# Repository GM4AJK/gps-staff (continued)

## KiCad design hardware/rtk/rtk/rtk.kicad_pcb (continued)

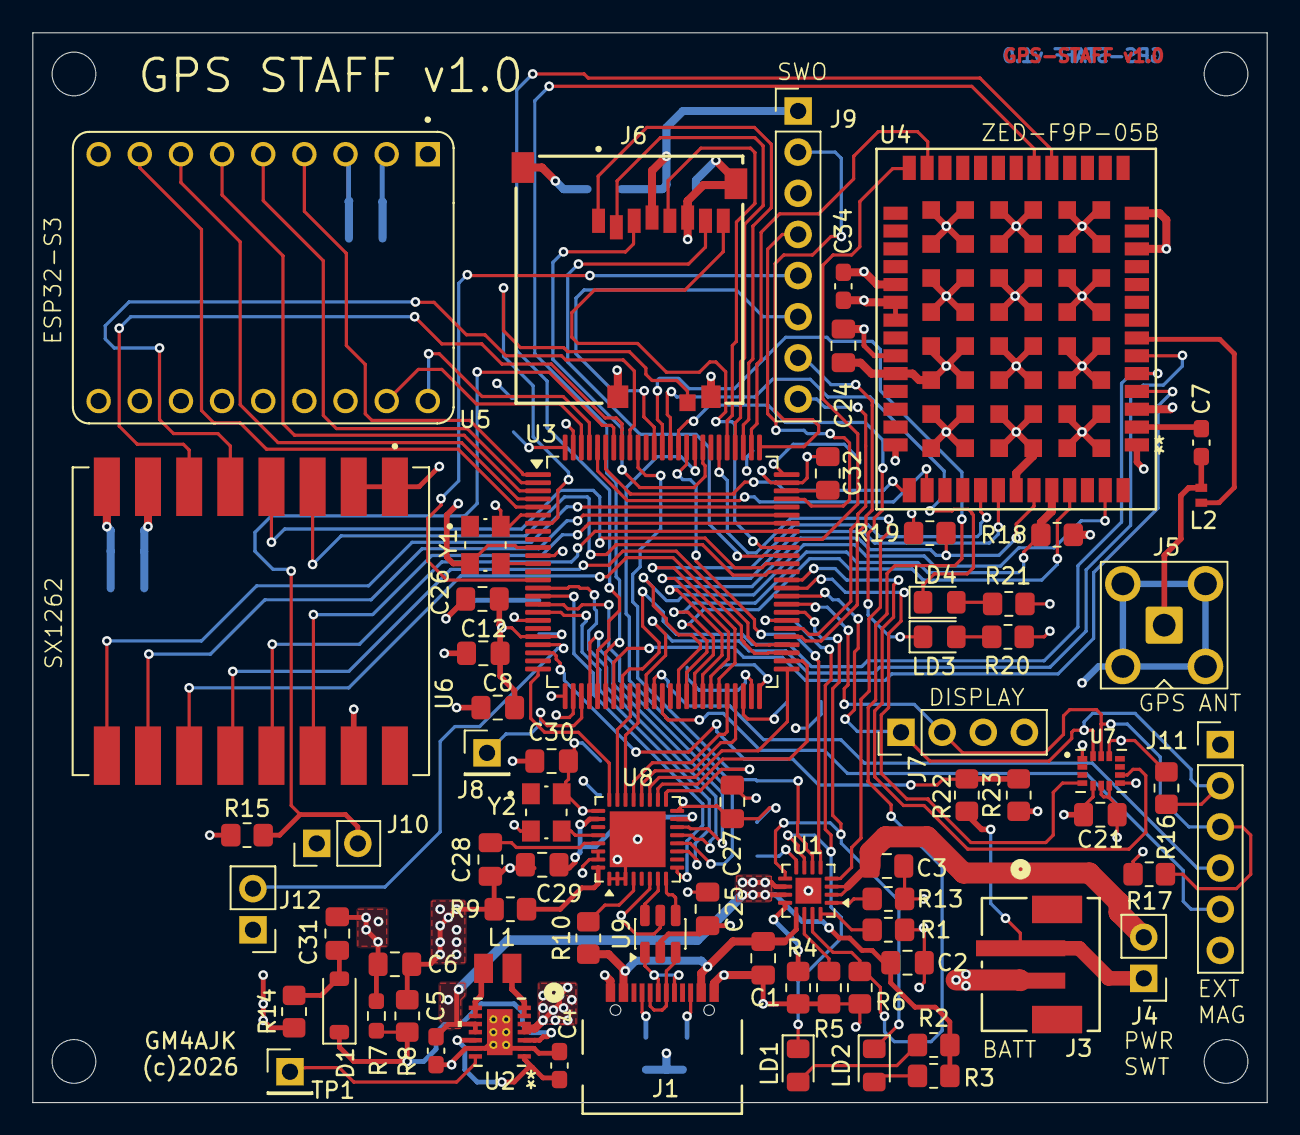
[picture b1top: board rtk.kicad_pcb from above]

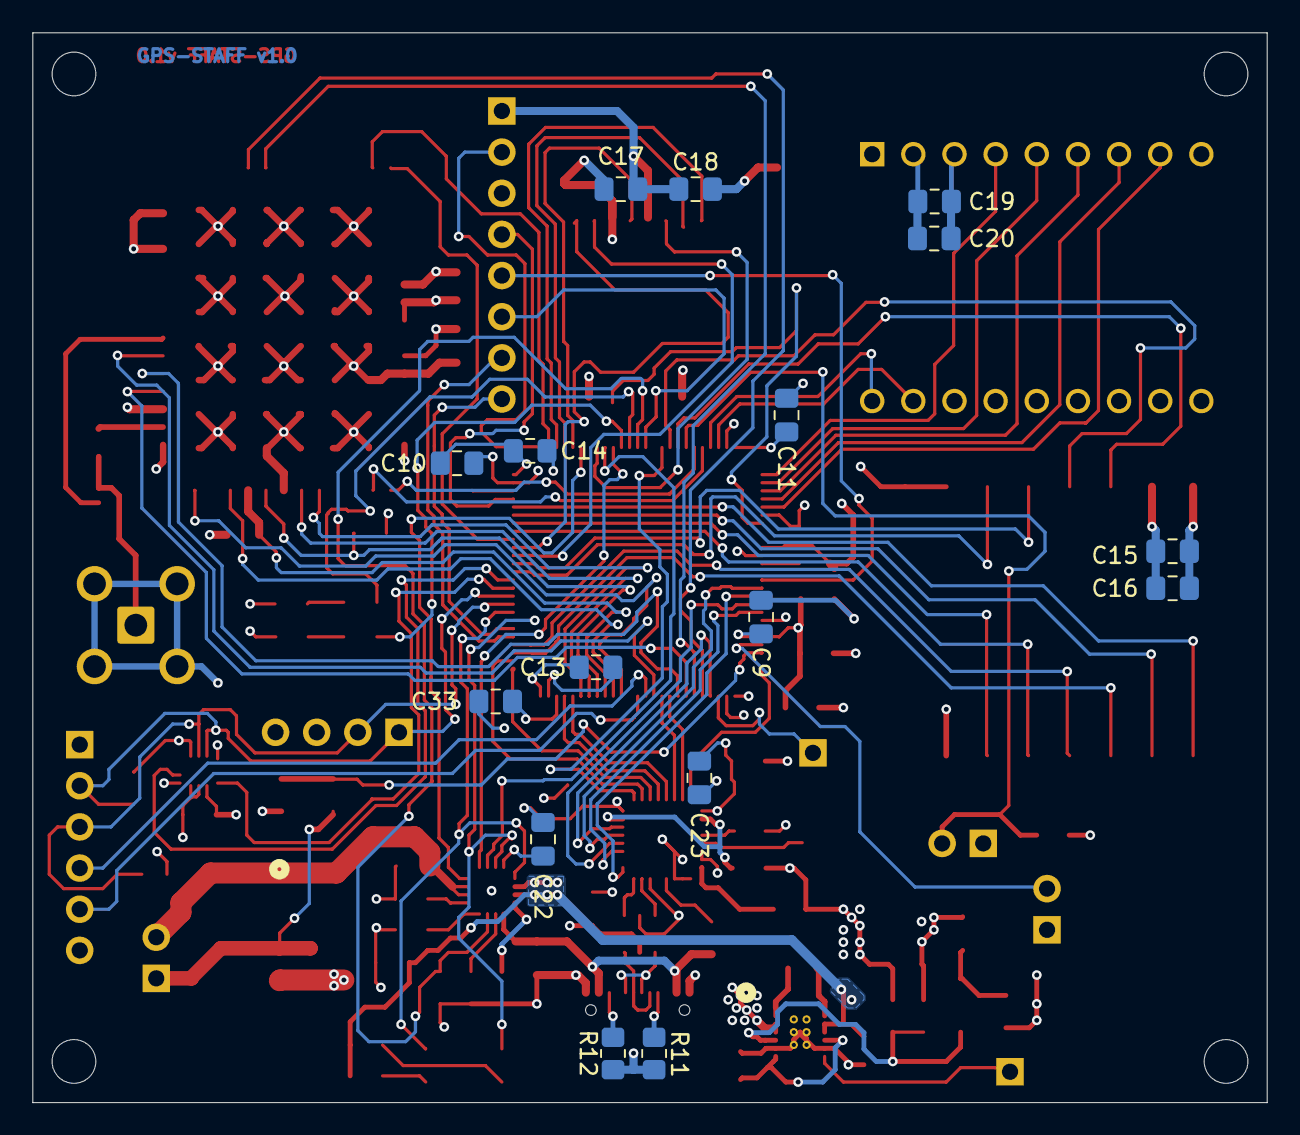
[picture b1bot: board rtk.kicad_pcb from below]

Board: 4 copper layers, 76.2 x 66.0 mm, 91 parts (16 on the bottom side), 113 nets.

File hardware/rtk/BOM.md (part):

# Schematic BOM — rtk PCB

Generated from KiCad schematics. One row per reference designator.
**Purpose:** footprint audit before PCB layout — verify every footprint against the actual part's datasheet land pattern.

Key:
- **Footprint** — KiCad library:footprint as currently assigned in the schematic
- **⚠** — suspected issue, needs checking before layout

---

## Capacitors

| Ref | Value | Footprint | Sheet | Notes |
|-----|-------|-----------|-------|-------|
| C1 | 1u | `C_0805_2012Metric_Pad1.18x1.45mm_HandSolder` | power | Tantallum (TAJR105M016RNJ) — verify 0805 land pattern matches AVX/Kyocera footprint |
| C2 | 4u7 | `C_0805_2012Metric_Pad1.18x1.45mm_HandSolder` | power | Tantalum (TAJP475K016RNJ) — same as C1 |
| C3 | 4u7 | `C_0805_2012Metric_Pad1.18x1.45mm_HandSolder` | power | Tantalum (TAJP475K016RNJ) — same as C1 |
| C4 | 100n | `C_0603_1608Metric_Pad1.08x0.95mm_HandSolder` | power | TPS63020 CvinA decoupling |
| C5 | 22u | `C_0603_1608Metric_Pad1.08x0.95mm_HandSolder` | power | TPS63020 Cin — part is C1608X5R1A226M080AC (0603/1608 metric) ✓ |
| C6 | 47u | `C_0805_2012Metric_Pad1.18x1.45mm_HandSolder` | power | TPS63020 Cout — part is MSASJ21GBB5476MTNA01 (0805/2012 metric) ✓ |
| C7 | 10n | `C_0603_1608Metric_Pad1.08x0.95mm_HandSolder` | zed-f9p-05b | VCC_RF decoupling |
| C8 | 100n | `C_0805_2012Metric_Pad1.18x1.45mm_HandSolder` | stm32f765vit | VDD decoupling |
| C9 | 100n | `C_0805_2012Metric_Pad1.18x1.45mm_HandSolder` | stm32f765vit | VDD decoupling |
| C10 | 100n | `C_0805_2012Metric_Pad1.18x1.45mm_HandSolder` | stm32f765vit | VDD decoupling |
| C11 | 100n | `C_0805_2012Metric_Pad1.18x1.45mm_HandSolder` | stm32f765vit | VDD decoupling |
| C12 | 100n | `C_0805_2012Metric_Pad1.18x1.45mm_HandSolder` | stm32f765vit | VDD decoupling |
| C13 | 100n | `C_0805_2012Metric_Pad1.18x1.45mm_HandSolder` | stm32f765vit | VDD decoupling |
| C14 | 100n | `C_0805_2012Metric_Pad1.18x1.45mm_HandSolder` | stm32f765vit | VDD decoupling |
| C15 | 100n | `C_0805_2012Metric_Pad1.18x1.45mm_HandSolder` | stm32f765vit | VDD decoupling |
| C16 | 10u | `C_0805_2012Metric_Pad1.18x1.45mm_HandSolder` | stm32f765vit | **T529P106M010AAE200** — Kemet KO-CAP polymer tant, 10µF 10V 0805, 200mΩ. Polarised symbol (C_Polarized_Small). ✓ |
| C17 | 100n | `C_0805_2012Metric_Pad1.18x1.45mm_HandSolder` | stm32f765vit | VDD decoupling |
| C18 | 10u | `C_0805_2012Metric_Pad1.18x1.45mm_HandSolder` | stm32f765vit | **T529P106M010AAE200** — same as C16 ✓ |
| C19 | 100n | `C_0805_2012Metric_Pad1.18x1.45mm_HandSolder` | stm32f765vit | VDD decoupling |
| C20 | 10u | `C_0805_2012Metric_Pad1.18x1.45mm_HandSolder` | stm32f765vit | **T529P106M010AAE200** — same as C16 ✓ |
| C21 | 100n | `C_0805_2012Metric_Pad1.18x1.45mm_HandSolder` | stm32f765vit | VDD decoupling |
| C22 | 100n | `C_0805_2012Metric_Pad1.18x1.45mm_HandSolder` | usb2hs | USB3300 decoupling |
| C23 | 100n | `C_0805_2012Metric_Pad1.18x1.45mm_HandSolder` | usb2hs | USB3300 decoupling |
| C24 | 100n | `C_0805_2012Metric_Pad1.18x1.45mm_HandSolder` | usb2hs | USB3300 decoupling |
| C25 | 100n | `C_0805_2012Metric_Pad1.18x1.45mm_HandSolder` | usb2hs | USB3300 decoupling |
| C26 | 100n | `C_0805_2012Metric_Pad1.18x1.45mm_HandSolder` | stm32f765vit | Decoupling |
| C27 | 100n | `C_0805_2012Metric_Pad1.18x1.45mm_HandSolder` | usb2hs | USB3300 decoupling |
| C28 | 470n | `C_0805_2012Metric_Pad1.18x1.45mm_HandSolder` | usb2hs | USB3300 VDD1.8 bulk |
| C29 | 470n | `C_0805_2012Metric_Pad1.18x1.45mm_HandSolder` | usb2hs | USB3300 VDD1.8 bulk |
| C30 | 100n | `C_0805_2012Metric_Pad1.18x1.45mm_HandSolder` | usb2hs | USB3300 decoupling |
| C31 | 10n | `C_0805_2012Metric_Pad1.18x1.45mm_HandSolder` | power | TPS63020 soft-start / inrush (C_SS) |
| C32 | 1u | `C_0805_2012Metric_Pad1.18x1.45mm_HandSolder` | stm32f765vit | STM32 VCAP_1 (internal LDO) |
| C33 | 1u | `C_0805_2012Metric_Pad1.18x1.45mm_HandSolder` | stm32f765vit | STM32 VCAP_2 (internal LDO) |
| C34 | 100n | `C_0603_1608Metric_Pad1.08x0.95mm_HandSolder` | zed-f9p-05b | V_BCKP decoupling |

---

## Resistors

| Ref | Value | Footprint | Sheet | Notes |
|-----|-------|-----------|-------|-------|
| R1 | 1k13 | `R_0805_2012Metric_Pad1.20x1.40mm_HandSolder` | power | BQ24075 ISET |
| R2 | 1K5 | `R_0805_2012Metric_Pad1.20x1.40mm_HandSolder` | power | BQ24075 nPGOOD LED pull-up |
| R3 | 1K5 | `R_0805_2012Metric_Pad1.20x1.40mm_HandSolder` | power | BQ24075 nCHG LED pull-up |
| R4 | 1k18 | `R_0805_2012Metric_Pad1.20x1.40mm_HandSolder` | power | BQ24075 — check function |
| R5 | 46k4 | `R_0805_2012Metric_Pad1.20x1.40mm_HandSolder` | power | BQ24075 TMR |
| R6 | 1k | `R_0805_2012Metric_Pad1.20x1.40mm_HandSolder` | power | LED current limit |
| R7 | 768k | `R_0805_2012Metric_Pad1.20x1.40mm_HandSolder` | power | TPS63020 Rfbt (FB top) |
| R8 | 137k | `R_0805_2012Metric_Pad1.20x1.40mm_HandSolder` | power | TPS63020 Rfbb (FB bottom) |
| R9 | 12k | `R_0805_2012Metric_Pad1.20x1.40mm_HandSolder` | usb2hs | USB3300 RBIAS |
| R10 | 10K | `R_0805_2012Metric_Pad1.20x1.40mm_HandSolder` | usb2hs | USB3300 VBUS protect |
| R11 | 5k1 | `R_0805_2012Metric_Pad1.20x1.40mm_HandSolder` | power | USB-C CC1 pull-down |
| R12 | 5k1 | `R_0805_2012Metric_Pad1.20x1.40mm_HandSolder` | power | USB-C CC2 pull-down |
| R13 | NF or 82k5 | `R_0805_2012Metric_Pad1.20x1.40mm_HandSolder` | power | TPS63020 TS pin (NF or 82k5 to set threshold) |
| R14 | NF or 1M | `R_0805_2012Metric_Pad1.20x1.40mm_HandSolder` | power | TPS63020 bleed resistor (NF or 1M) |
| R15 | 1k | `R_0805_2012Metric_Pad1.20x1.40mm_HandSolder` | stm32f765vit | BOOT0 pull-down |
| R16 | 4k7 | `R_0805_2012Metric_Pad1.20x1.40mm_HandSolder` | stm32f765vit | I2C4 SDA pull-up |
| R17 | 4k7 | `R_0805_2012Metric_Pad1.20x1.40mm_HandSolder` | stm32f765vit | I2C4 SCL pull-up |
| R18 | 10k | `R_0805_2012Metric_Pad1.20x1.40mm_HandSolder` | zed-f9p-05b | ZED-F9P SAFEBOOT_N pull-up |
| R19 | 10k | `R_0805_2012Metric_Pad1.20x1.40mm_HandSolder` | zed-f9p-05b | ZED-F9P RESET_N pull-up |
| R20 | 1k5 | `R_0805_2012Metric_Pad1.20x1.40mm_HandSolder` | stm32f765vit | LD3 pull-up (PD5) |
| R21 | 1k5 | `R_0805_2012Metric_Pad1.20x1.40mm_HandSolder` | stm32f765vit | LD4 pull-up (PD6) |
| R22 | 100k | `R_0805_2012Metric_Pad1.20x1.40mm_HandSolder` | power | VBAT divider top — VBAT to VBAT_2 |
| R23 | 100k | `R_0805_2012Metric_Pad1.20x1.40mm_HandSolder` | power | VBAT divider bottom — VBAT_2 to GND → PA1 ADC1_IN1 |

---

## Inductors

| Ref | Value | Footprint | Sheet | Notes |
|-----|-------|-----------|-------|-------|
| L1 | 1uH | `IND_DFE2016_2X1P6_MUR` | power | TPS63020 switching inductor — verify custom footprint matches DFE201610E-1R0M |
| L2 | 8n | `L_0402_1005Metric` | zed-f9p-05b | Bias-T RF choke — LQW15AN8N0G8ZD (Murata, 8.0nH ±2%, wire-wound 0402) [DigiKey](https://www.digikey.co.uk/en/products/detail/murata-electron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 |

---

## Diodes / ESD / LED

| Ref | Value | Footprint | Sheet | Notes |
|-----|-------|-----------|-------|-------|
| D1 | 1N4148W | `D_SOD-123` | power | TPS63020 inrush diode |
| D2 | USBLC6-2SC6 | `SOT-23-6` | usb2hs | USB D+/D- dual-line ESD TVS — replaced PRTR5V0U2X (bulk only). D3 removed (one chip covers both lines) ✓ |
| LD1 | LED | `LED_0805_2012Metric_Pad1.15x1.40mm_HandSolder` | power | **Green** — nPGOOD status |
| LD2 | LED | `LED_0805_2012Metric_Pad1.15x1.40mm_HandSolder` | power | **Red** — nCHG status |
| LD3 | LED | `LED_0805_2012Metric_Pad1.15x1.40mm_HandSolder` | stm32f765vit | **Green** — debug/status, PD5, open-drain, on at startup |
| LD4 | LED | `LED_0805_2012Metric_Pad1.15x1.40mm_HandSolder` | stm32f765vit | **Red** — debug/status, PD6, open-drain, on at startup |

---

## ICs / Modules

| Ref | Value | Footprint | Sheet | Notes |
|-----|-------|-----------|-------|-------|
| U1 | BQ24075RGT | `VQFN-16-1EP_3x3mm_P0.5mm_EP1.6x1.6mm` | power | Battery charger / power path |
| U2 | TPS63020DSJR | `DSJ14_2P85X1P58` | power | Buck-boost — verify custom footprint matches VSON-14 land pattern in TPS63020 datasheet |
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
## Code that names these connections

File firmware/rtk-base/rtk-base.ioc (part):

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Mcu.Name=STM32F765V(G-I)Tx
Mcu.Package=LQFP100
Mcu.UserName=STM32F765VITx
PA0/WKUP.GPIOParameters=GPIO_PuPd,GPIO_Label
PA0/WKUP.GPIO_Label=BASE_ROVER_MODE_SELECT
PA0/WKUP.GPIO_PuPd=GPIO_PULLUP
PA0/WKUP.Signal=GPIO_Input
PA1.GPIOParameters=GPIO_Label
PA1.GPIO_Label=VBATT_IN
PA1.Signal=ADCx_IN1
PA10.GPIOParameters=PinState,GPIO_Label
PA10.GPIO_Label=SX1262_SPI2_CS
PA10.PinState=GPIO_PIN_SET
PA10.Signal=GPIO_Output
PA11.GPIOParameters=GPIO_Label
PA11.GPIO_Label=SX1262_SPI2_RST
PA11.Signal=GPIO_Output
PA12.GPIOParameters=GPIO_PuPd,GPIO_Label
PA12.GPIO_Label=SX1262_SPI2_BUSY
PA12.GPIO_PuPd=GPIO_PULLUP
PA12.Signal=GPIO_Input
PA13.Mode=Serial_Wire
PA13.Signal=SYS_JTMS-SWDIO
PA14.Mode=Serial_Wire
PA14.Signal=SYS_JTCK-SWCLK
PA15.GPIOParameters=GPIO_Label
PA15.GPIO_Label=UART7T_X_F9P_RXD2
PA15.Mode=Asynchronous
PA15.Signal=UART7_TX
PA3.Mode=Device_HS
PA3.Signal=USB_OTG_HS_ULPI_D0
PA4.Mode=Activate_SOF_FS
PA4.Signal=USB_OTG_HS_SOF
PA5.Mode=Device_HS
PA5.Signal=USB_OTG_HS_ULPI_CK
PA6.GPIOParameters=GPIO_Label
PA6.GPIO_Label=F9P_GEOFENCH_STAT
PA6.Signal=GPIO_Input
PA7.GPIOParameters=GPIO_Label
PA7.GPIO_Label=F9P_RTK_STAT
PA7.Signal=GPIO_Input
PA8.GPIOParameters=GPIO_Label
PA8.GPIO_Label=UART7_RX_F9P_TXD2
PA8.Mode=Asynchronous
PA8.Signal=UART7_RX
PA9.GPIOParameters=GPIO_Label
PA9.GPIO_Label=SX1262_SPI_CLK
PA9.Mode=Full_Duplex_Master
PA9.Signal=SPI2_SCK
PB0.Mode=Device_HS
PB0.Signal=USB_OTG_HS_ULPI_D1
PB1.Mode=Device_HS
PB1.Signal=USB_OTG_HS_ULPI_D2
PB10.Mode=Device_HS
PB10.Signal=USB_OTG_HS_ULPI_D3
PB11.Mode=Device_HS
PB11.Signal=USB_OTG_HS_ULPI_D4
PB12.Mode=Device_HS
PB12.Signal=USB_OTG_HS_ULPI_D5
PB13.Mode=Device_HS
PB13.Signal=USB_OTG_HS_ULPI_D6
PB14.GPIOParameters=GPIO_Label
PB14.GPIO_Label=SX1262_SPI_MISO
PB14.Mode=Full_Duplex_Master
PB14.Signal=SPI2_MISO
PB15.GPIOParameters=GPIO_Label
PB15.GPIO_Label=SX1262_SPI_MOSI
PB15.Mode=Full_Duplex_Master
PB15.Signal=SPI2_MOSI
PB2.GPIOParameters=GPIO_Label
PB2.GPIO_Label=F9P_ANT_SHORT_N
PB2.Signal=GPIO_Input
PB3.Signal=SYS_JTDO-SWO
PB5.Mode=Device_HS
PB5.Signal=USB_OTG_HS_ULPI_D7
PB6.GPIOParameters=GPIO_Label
PB6.GPIO_Label=SX1262_SPI2_DIO2
PB6.Signal=GPIO_Output
PB7.GPIOParameters=GPIO_Label
PB7.GPIO_Label=SX1262_SPI2_DIO1
PB7.Signal=GPIO_Input
PB8.GPIOParameters=GPIO_Label
PB8.GPIO_Label=F9P_RX
PB8.Mode=Asynchronous
PB8.Signal=UART5_RX
PB9.GPIOParameters=GPIO_Label
PB9.GPIO_Label=F9P_TX
PB9.Mode=Asynchronous
PB9.Signal=UART5_TX
PC0.Mode=Device_HS
PC0.Signal=USB_OTG_HS_ULPI_STP
PC1.GPIOParameters=GPIO_Speed,GPIO_Label
PC1.GPIO_Label=USB3300_RST
PC1.GPIO_Speed=GPIO_SPEED_FREQ_HIGH
PC1.Signal=GPIO_Output
PC10.Mode=SD_4_bits_Wide_bus
PC10.Signal=SDMMC1_D2
PC11.Mode=SD_4_bits_Wide_bus
PC11.Signal=SDMMC1_D3
PC12.Mode=SD_4_bits_Wide_bus
PC12.Signal=SDMMC1_CK
PC13.GPIOParameters=GPIO_PuPd,GPIO_Label
PC13.GPIO_Label=SDMMC_CD
PC13.GPIO_PuPd=GPIO_PULLUP
PC13.Signal=GPIO_Input
PC2.Mode=Device_HS
PC2.Signal=USB_OTG_HS_ULPI_DIR
PC3.Mode=Device_HS
PC3.Signal=USB_OTG_HS_ULPI_NXT
PC4.GPIOParameters=GPIO_Label
PC4.GPIO_Label=F9P_ANT_DETECT
PC4.Signal=GPIO_Input
PC5.GPIOParameters=GPIO_Label
PC5.GPIO_Label=F9P_ANT_OFF
PC5.Signal=GPIO_Output
PC6.GPIOParameters=GPIO_Label
PC6.GPIO_Label=SX1262_RXEN
PC6.Signal=GPIO_Output
PC7.GPIOParameters=GPIO_Label
PC7.GPIO_Label=SX1262T_XEN
PC7.Signal=GPIO_Output
PC8.Mode=SD_4_bits_Wide_bus
PC8.Signal=SDMMC1_D0
PC9.Mode=SD_4_bits_Wide_bus
PC9.Signal=SDMMC1_D1
PD0.GPIOParameters=GPIO_Label
PD0.GPIO_Label=BQ24975_nCE
PD0.Signal=GPIO_Output
PD10.GPIOParameters=GPIO_Label
PD10.GPIO_Label=nPGOOD
PD10.Signal=GPIO_Input
PD11.GPIOParameters=GPIO_Label
PD11.GPIO_Label=nCHG
PD11.Signal=GPIO_Input
PD12.Mode=I2C
PD12.Signal=I2C4_SCL
PD13.Mode=I2C
PD13.Signal=I2C4_SDA
PD14.GPIOParameters=GPIO_Label
PD14.GPIO_Label=LSM6DSOX_INT1
PD14.Signal=GPIO_Input
PD15.GPIOParameters=GPIO_Label
PD15.GPIO_Label=LSM6DSOX_INT2
PD15.Signal=GPIO_Input
PD2.Mode=SD_4_bits_Wide_bus
PD2.Signal=SDMMC1_CMD
PD3.GPIOParameters=PinState,GPIO_Label
PD3.GPIO_Label=BQ24975_EN1
PD3.PinState=GPIO_PIN_SET
PD3.Signal=GPIO_Output
PD4.GPIOParameters=PinState,GPIO_Label
PD4.GPIO_Label=BQ24975_EN2
PD4.PinState=GPIO_PIN_RESET
PD4.Signal=GPIO_Output
PD5.GPIOParameters=GPIO_PuPd,GPIO_Label,GPIO_ModeDefaultOutputPP
PD5.GPIO_Label=PD5_LD3
PD5.GPIO_ModeDefaultOutputPP=GPIO_MODE_OUTPUT_OD
PD5.GPIO_PuPd=GPIO_NOPULL
PD5.Signal=GPIO_Output
PD6.GPIOParameters=GPIO_PuPd,GPIO_Label,GPIO_ModeDefaultOutputPP
PD6.GPIO_Label=PD6_LD4
PD6.GPIO_ModeDefaultOutputPP=GPIO_MODE_OUTPUT_OD
PD6.GPIO_PuPd=GPIO_NOPULL
PD6.Signal=GPIO_Output
PD7.GPIOParameters=GPIO_Label
PD7.GPIO_Label=SYSOFF
PD7.Signal=GPIO_Output
PD8.GPIOParameters=GPIO_Label
PD8.GPIO_Label=DEBUG_TX
PD8.Mode=Asynchronous
PD8.Signal=USART3_TX
PD9.GPIOParameters=GPIO_Label
PD9.GPIO_Label=DEBUG_RX
PD9.Mode=Asynchronous
PD9.Signal=USART3_RX
PE0.Mode=Asynchronous
PE0.Signal=UART8_RX
PE1.Mode=Asynchronous
PE1.Signal=UART8_TX
PE10.GPIOParameters=GPIO_Label
PE10.GPIO_Label=F9P_TIMEP
PE10.Signal=GPXTI10
PE11.GPIOParameters=GPIO_Label
PE11.GPIO_Label=F9P_EXTINT
PE11.Signal=GPXTI11
PE12.GPIOParameters=PinState,GPIO_Label
PE12.GPIO_Label=F9P_SAFEBOOT_N
PE12.PinState=GPIO_PIN_SET
PE12.Signal=GPIO_Output
PE13.GPIOParameters=PinState,GPIO_Label
PE13.GPIO_Label=F9P_RESET_N
PE13.PinState=GPIO_PIN_SET
PE13.Signal=GPIO_Output
PE14.GPIOParameters=PinState,GPIO_Label
PE14.GPIO_Label=F9P_D_SEL
PE14.PinState=GPIO_PIN_SET
PE14.Signal=GPIO_Output
PE15.GPIOParameters=GPIO_Label
PE15.GPIO_Label=F9P_TX_READY
PE15.Signal=GPXTI15
PE2.GPIOParameters=GPIO_Label
PE2.GPIO_Label=ESP32_GP1
PE2.Signal=GPIO_Output
PE3.GPIOParameters=GPIO_Label
PE3.GPIO_Label=ESP32_GP2
PE3.Signal=GPIO_Output
PE4.GPIOParameters=GPIO_Label
PE4.GPIO_Label=ESP32_GP3
PE4.Signal=GPIO_Output
PE5.GPIOParameters=GPIO_Label
PE5.GPIO_Label=ESP32_GP4
PE5.Signal=GPIO_Output
PE6.GPIOParameters=GPIO_Label
PE6.GPIO_Label=ESP32_GP5
PE6.Signal=GPIO_Output
PE7.GPIOParameters=GPIO_Label
PE7.GPIO_Label=MAGNETO_SPARE1
PE7.Signal=GPIO_Output
PE8.GPIOParameters=GPIO_Label
PE8.GPIO_Label=MAGNETO_SPARE2
PE8.Signal=GPIO_Output
PH0/OSC_IN.Mode=HSE-External-Oscillator
PH0/OSC_IN.Signal=RCC_OSC_IN
PH1/OSC_OUT.Mode=HSE-External-Oscillator
PH1/OSC_OUT.Signal=RCC_OSC_OUT
RCC.HSE_VALUE=16000000
RCC.SYSCLKFreq_VALUE=216000000
RCC.SYSCLKSource=RCC_SYSCLKSOURCE_PLLCLK
board=custom

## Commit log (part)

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2026-06-19 RTCM3/LoRa OTA task for F767ZI FreeRTOS base station (#165)
    Adds task_ota: RTCM3 framing from Fake-F9P UART + SX1262 GFSK OTA TX.
    ISR reads USART2 RDR directly at register level, pushes bytes to a
    FreeRTOS queue; OTA task drains queue and feeds rtcm3_process_byte().
    No HAL in the interrupt path.
    Bench-verified: RTCM3 frames (1005/1074/1084/1094/1124) confirmed on
    SDR; Fake-F9P rover shows SYNCED with stable sync tracking.
